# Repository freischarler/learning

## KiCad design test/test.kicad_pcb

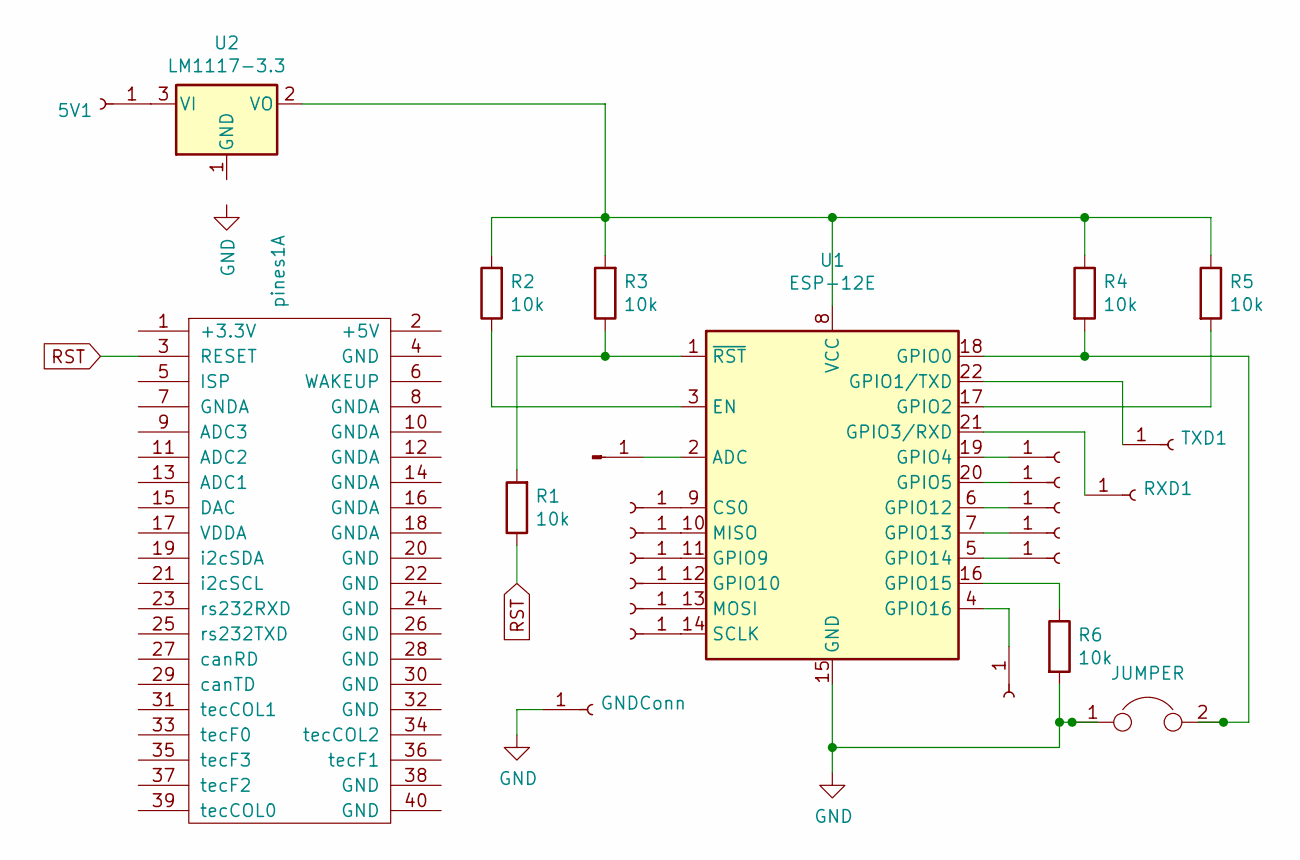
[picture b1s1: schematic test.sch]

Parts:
5V1: Conn_01x01_Male; PinHeader_1x01_P1.00mm_Vertical
ADC1: ADC; PinHeader_1x01_P1.00mm_Vertical
CSO1: 9; PinHeader_1x01_P1.00mm_Vertical
GNDConn: Conn_01x01_Male; PinHeader_1x01_P1.00mm_Vertical
GPIO4: P19; PinHeader_1x01_P1.00mm_Vertical
GPIO5: 20; PinHeader_1x01_P1.00mm_Vertical
GPIO9: 11; PinHeader_1x01_P1.00mm_Vertical
GPIO10: 12; PinHeader_1x01_P1.00mm_Vertical
GPIO12: 6; PinHeader_1x01_P1.00mm_Vertical
GPIO13: 7; PinHeader_1x01_P1.00mm_Vertical
GPIO14: 5; PinHeader_1x01_P1.00mm_Vertical
JUMPER1: JUMPER; SolderJumper-2_P1.3mm_Bridged2Bar_Pad1.0x1.5mm
MISO1: 10; PinHeader_1x01_P1.00mm_Vertical
MOSI1: 13; PinHeader_1x01_P1.00mm_Vertical
P4: 4; PinHeader_1x01_P1.00mm_Vertical
P14: 14; PinHeader_1x01_P1.00mm_Vertical
R1, R2, R3, R4, R5, R6: 10k; R_Axial_DIN0207_L6.3mm_D2.5mm_P7.62mm_Horizontal
RXD1: Conn_01x01_Male; PinHeader_1x01_P1.00mm_Vertical
TXD1: Conn_01x01_Male; PinHeader_1x01_P1.00mm_Vertical
U1: ESP-12E
U2: LM1117-3.3; SOT-23
pines1: Conn_02x20_Top_Bottom; Conn_Poncho_SinBorde

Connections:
GND: GNDConn.1, JUMPER1.1, R6.2, U1.15 (GND); also elsewhere on the board
unnamed: 5V1.1, U2.3 (VI)
unnamed: ADC1.1, U1.2 (ADC)
unnamed: CSO1.1, U1.9 (CS0)
unnamed: GPIO4.1, U1.19 (GPIO4)
unnamed: GPIO5.1, U1.20 (GPIO5)
unnamed: GPIO9.1, U1.11 (GPIO9)
unnamed: GPIO10.1, U1.12 (GPIO10)
unnamed: GPIO12.1, U1.6 (GPIO12)
unnamed: GPIO13.1, U1.7 (GPIO13)
unnamed: GPIO14.1, U1.5 (GPIO14)
unnamed: JUMPER1.2, R4.2, U1.18 (GPIO0)
unnamed: MISO1.1, U1.10 (MISO)
unnamed: MOSI1.1, U1.13 (MOSI)
unnamed: P4.1, U1.4 (GPIO16)
unnamed: P14.1, U1.14 (SCLK)
unnamed: R1.2, R3.1, U1.1 (~RST)
unnamed: R2.1, U1.3 (EN)
unnamed: R2.2, R3.2, R4.1, R5.1, U1.8 (VCC), U2.2 (VO)
unnamed: R5.2, U1.17 (GPIO2)
unnamed: R6.1, U1.16 (GPIO15)
unnamed: RXD1.1, U1.21 (GPIO3/RXD)
unnamed: TXD1.1, U1.22 (GPIO1/TXD)
RST: R1.1, pines1.3 (RESET)

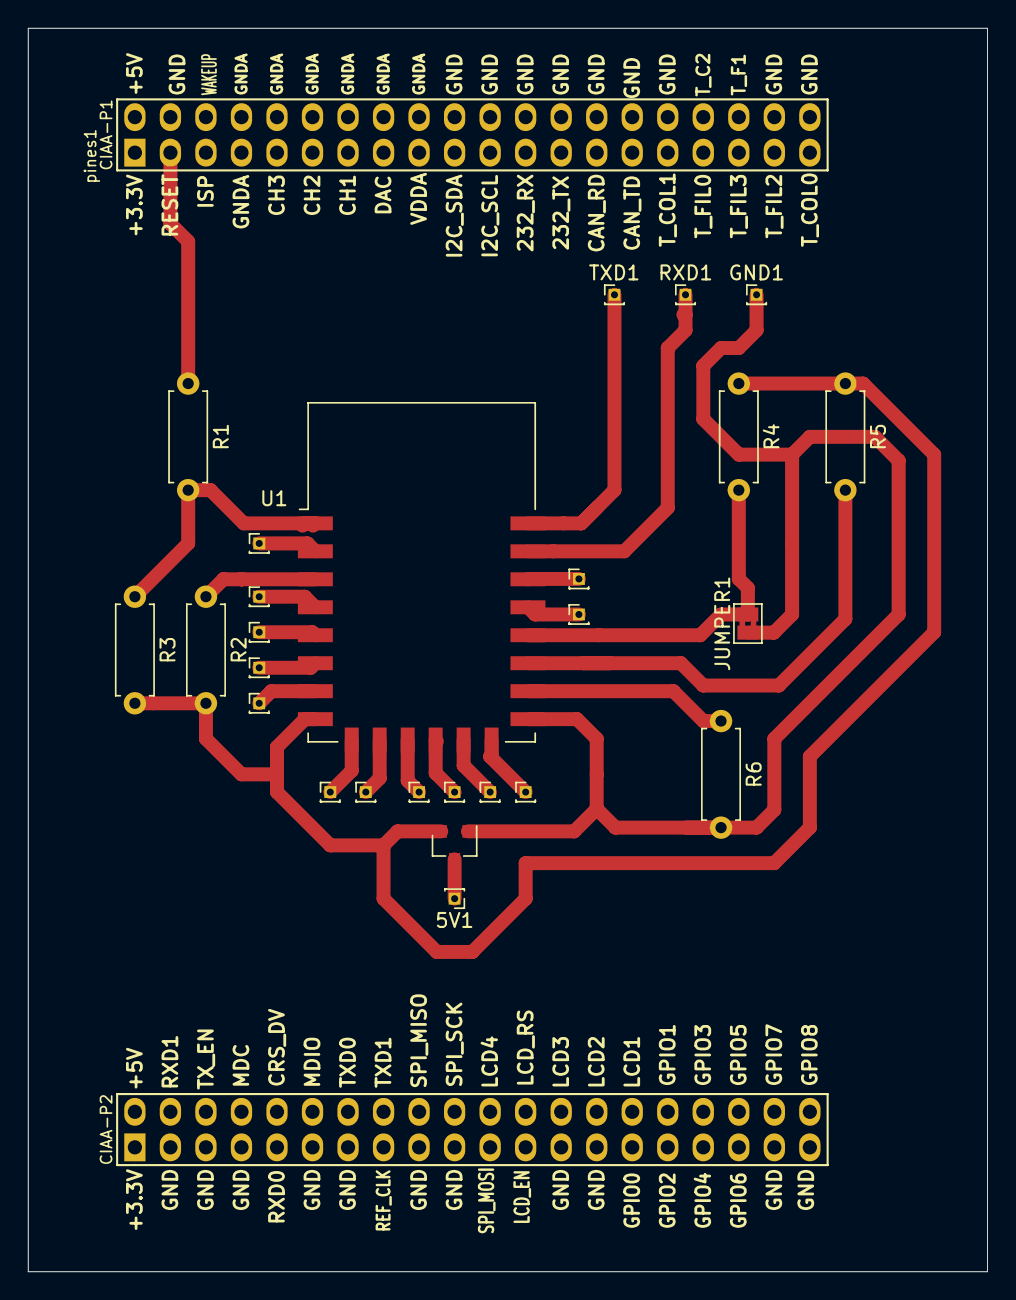
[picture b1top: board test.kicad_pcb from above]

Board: 2 copper layers, 68.6 x 88.9 mm, 27 parts (0 on the bottom side), 24 nets.

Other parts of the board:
GND1: Conn_01x01_Male; PinHeader_1x01_P1.00mm_Vertical

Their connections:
GND: GND1.1; also elsewhere on the board

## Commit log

2019-08-25 creando el index
